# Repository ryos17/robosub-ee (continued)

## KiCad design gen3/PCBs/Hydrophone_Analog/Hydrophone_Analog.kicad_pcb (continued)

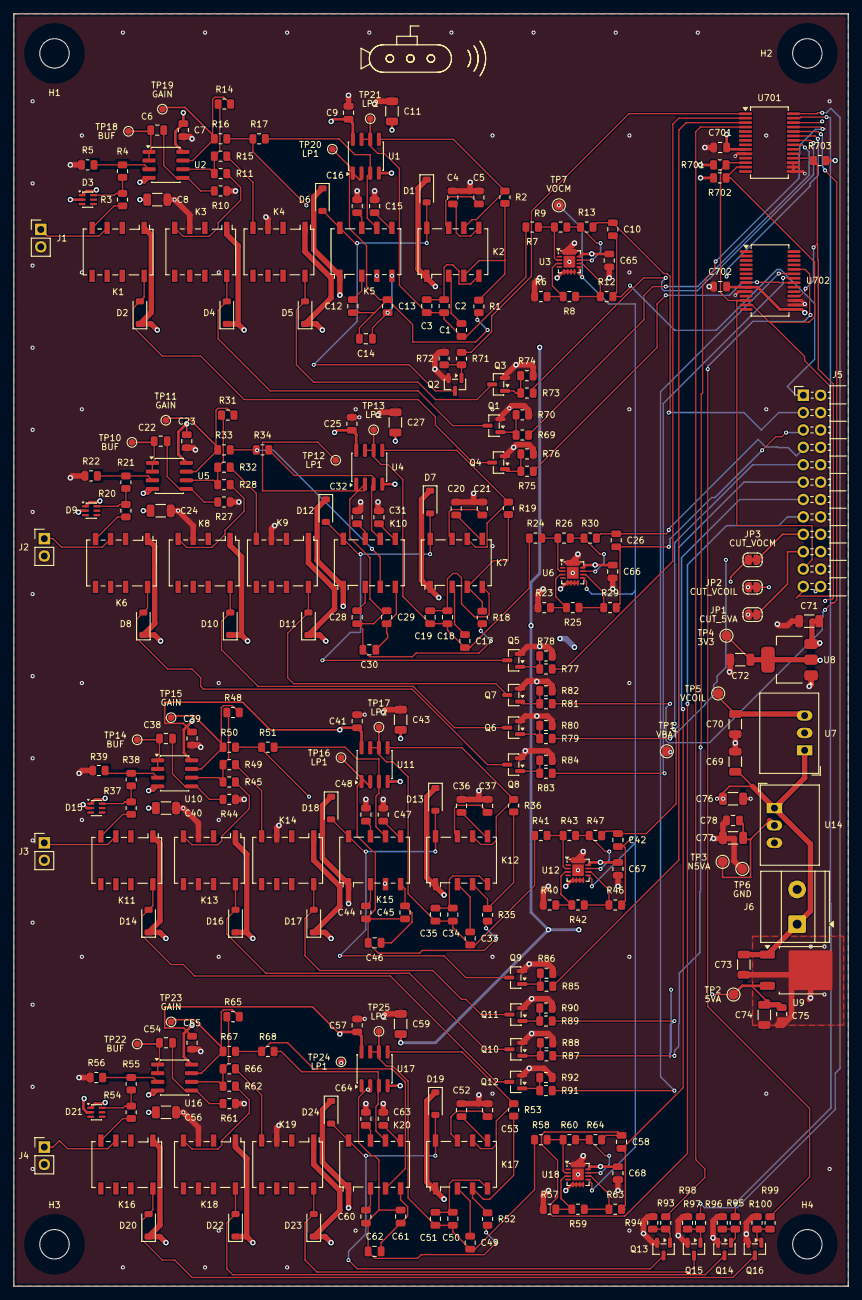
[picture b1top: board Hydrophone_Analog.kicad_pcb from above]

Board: 4 copper layers, 121.9 x 185.9 mm, 297 parts (0 on the bottom side), 181 nets.

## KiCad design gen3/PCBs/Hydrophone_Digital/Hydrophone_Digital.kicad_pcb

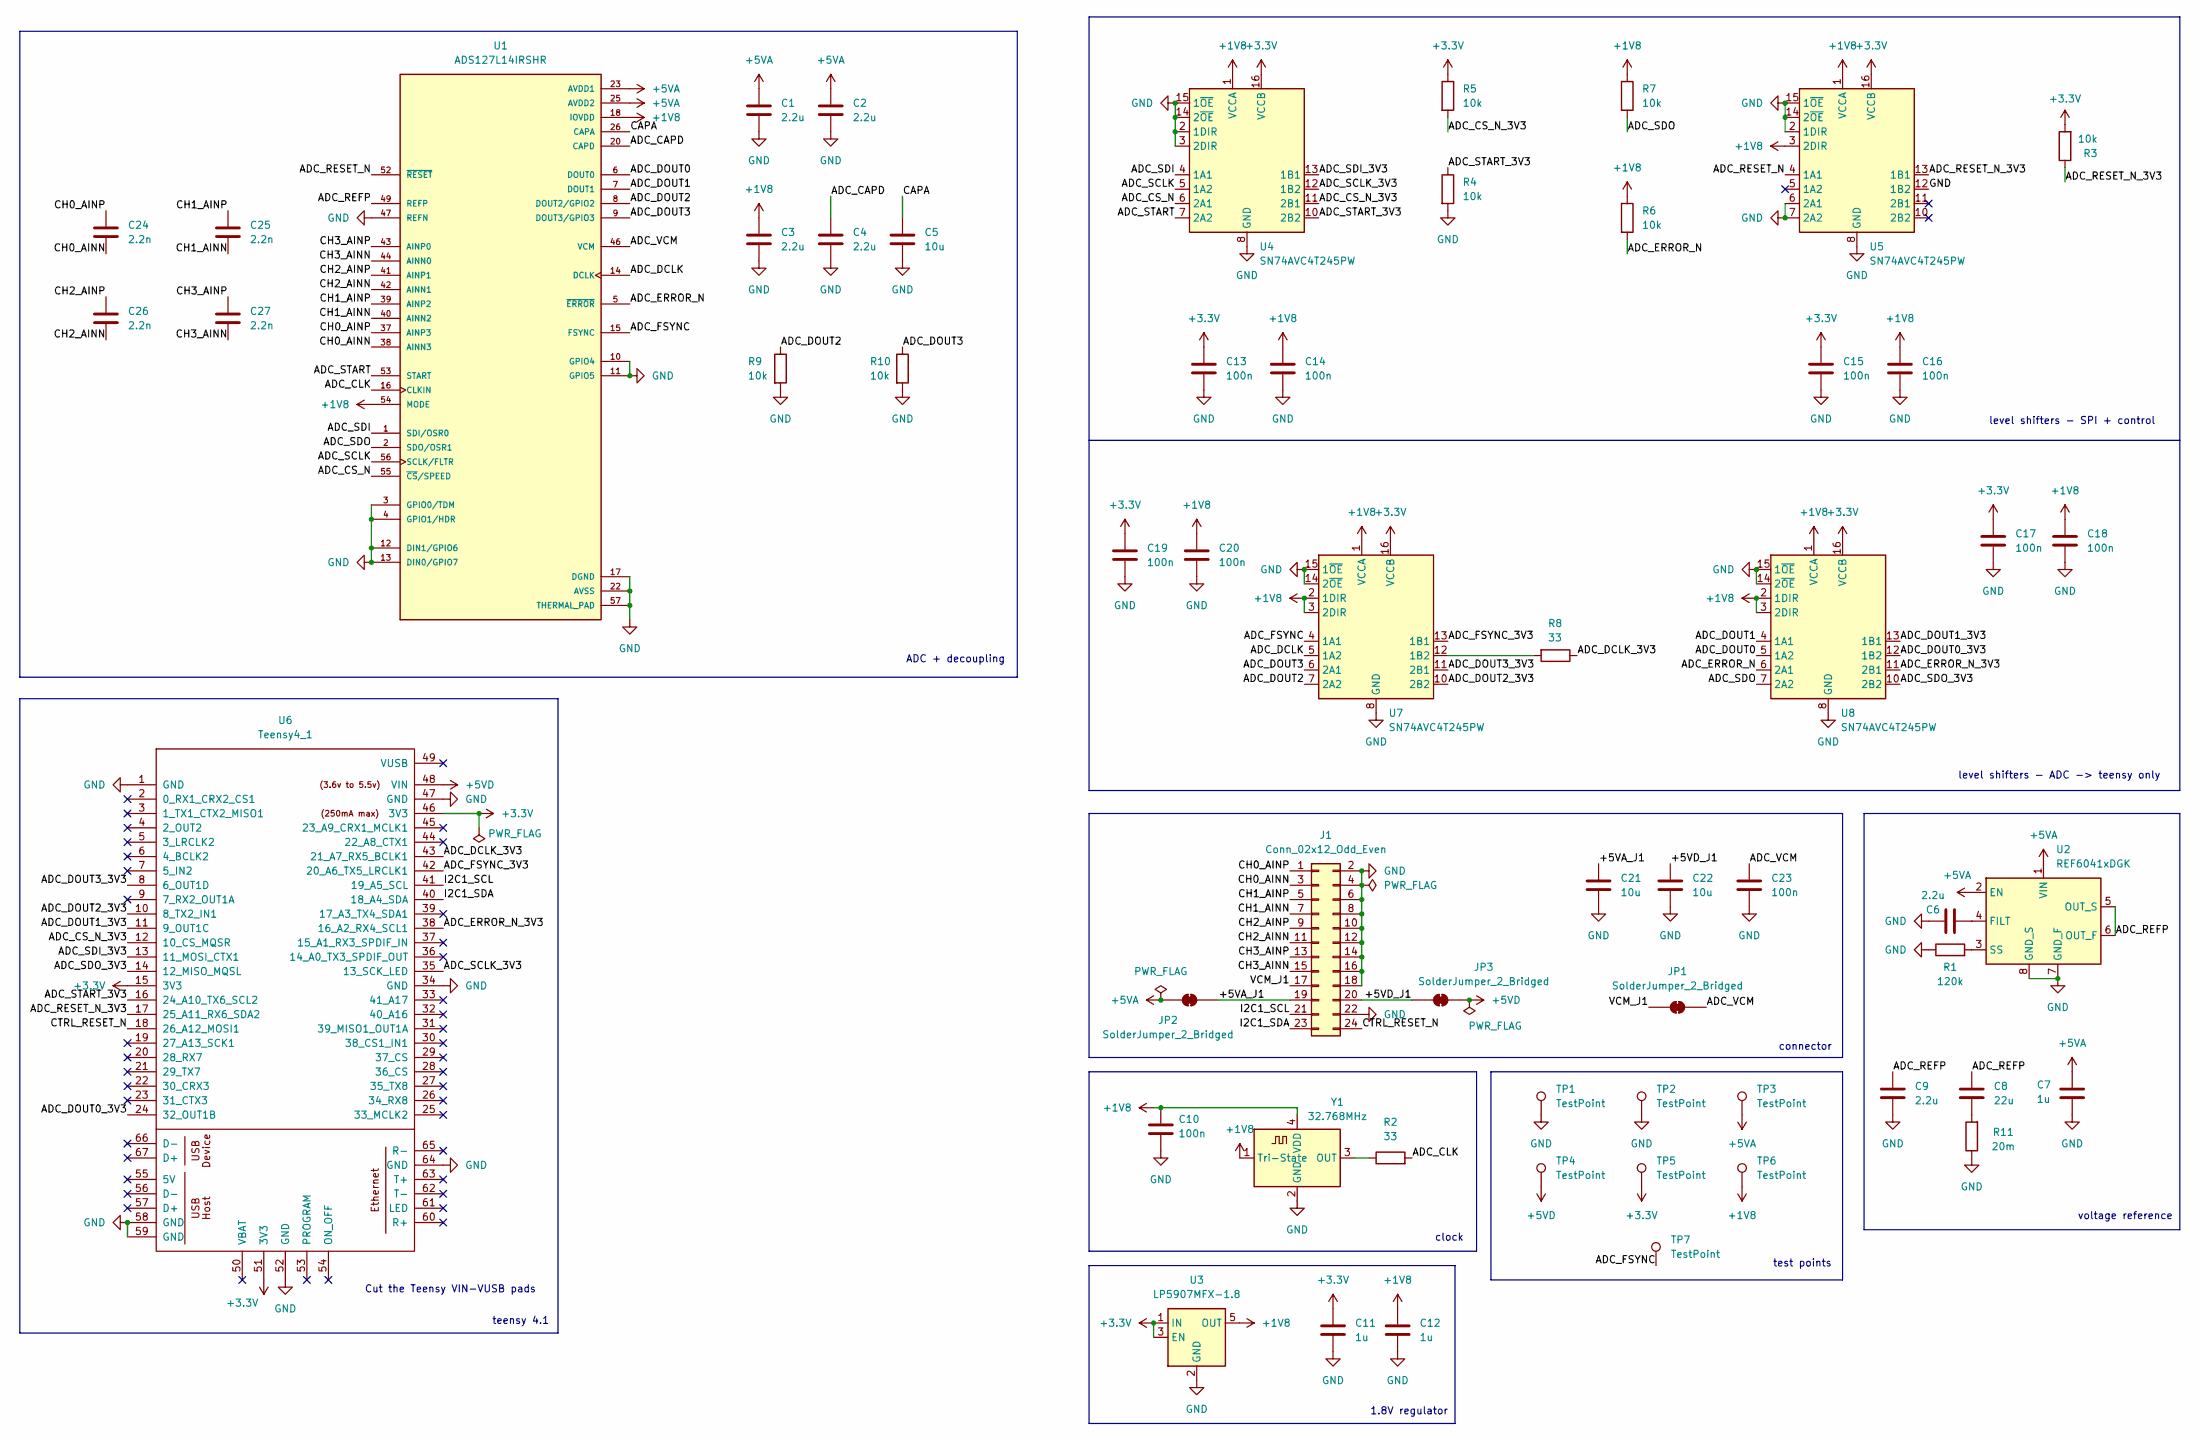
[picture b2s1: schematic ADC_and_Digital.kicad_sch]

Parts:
C1, C2, C3, C4, C6, C9: 2.2u; C_0805_2012Metric_Pad1.18x1.45mm_HandSolder; LCSC C19110
C5, C21, C22: 10u; C_1206_3216Metric_Pad1.33x1.80mm_HandSolder; LCSC C13585
C7, C11, C12: 1u; C_0805_2012Metric_Pad1.18x1.45mm_HandSolder; LCSC C28323
C8: 22u; C_1206_3216Metric_Pad1.33x1.80mm_HandSolder; LCSC C12891
C10, C13, C14, C15, C16, C17, C18, C19, C20, C23: 100n; C_0805_2012Metric_Pad1.18x1.45mm_HandSolder; LCSC C49678
C24, C25, C26, C27: 2.2n; C_0805_2012Metric_Pad1.18x1.45mm_HandSolder; LCSC C28260
J1: Conn_02x12_Odd_Even; PinSocket_2x12_P2.54mm_Horizontal; LCSC C22373936
JP1, JP2, JP3: SolderJumper_2_Bridged; SolderJumper-2_P1.3mm_Bridged_RoundedPad1.0x1.5mm
R1: 120k; R_0805_2012Metric_Pad1.20x1.40mm_HandSolder; LCSC C17436
R2, R8: 33; R_0805_2012Metric_Pad1.20x1.40mm_HandSolder; LCSC C17634
R3, R4, R5, R6, R7, R9, R10: 10k; R_0805_2012Metric_Pad1.20x1.40mm_HandSolder; LCSC C17414
R11: 20m; R_0805_2012Metric_Pad1.20x1.40mm_HandSolder; LCSC C163095
TP1, TP2, TP3, TP4: TestPoint; TestPoint_THTPad_D2.0mm_Drill1.0mm
TP5, TP6: TestPoint; TestPoint_Pad_D1.5mm
TP7: TestPoint; TestPoint_Pad_D1.0mm
U1: ADS127L14IRSHR; IC_ADS127L14IRSHR; PARTREV B; LCSC C46377303
U2: REF6041xDGK; VSSOP-8_3x3mm_P0.65mm; LCSC C2157051
U3: LP5907MFX-1.8; SOT-23-5; LCSC C92498
U4, U5, U7, U8: SN74AVC4T245PW; TSSOP-16_4.4x5mm_P0.65mm; LCSC C81461
U6: Teensy4_1
Y1: 32.768MHz; Oscillator_SMD_ECS_2520MV-xxx-xx-4Pin_2.5x2.0mm; LCSC C5452669

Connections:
+1V8: C3.2, C10.1, C12.1, C14.1, C16.1, C18.1, C20.1, R6.1, R7.1, TP6.1 (1_1), U1.18 (IOVDD), U1.19 (IOVDD), U1.54 (MODE), U3.5 (OUT), U4.1 (VCCA), U5.1 (VCCA), U5.3 (2DIR), U7.1 (VCCA), U7.2 (1DIR), U7.3 (2DIR), U8.1 (VCCA), U8.2 (1DIR), U8.3 (2DIR), Y1.1 (Tri-State), Y1.4 (VDD)
+3.3V: C11.1, C13.1, C15.1, C17.1, C19.1, R3.2, R5.1, TP5.1 (1_1), U3.1 (IN), U3.3 (EN), U4.16 (VCCB), U5.16 (VCCB), U6.15 (3V3), U6.46 (3V3), U6.51 (3V3), U7.16 (VCCB), U8.16 (VCCB)
+5VA: C1.2, C2.2, C7.1, JP2.1 (A), TP3.1 (1_1), U1.23 (AVDD1), U1.24 (AVDD1), U1.25 (AVDD2), U2.1 (VIN), U2.2 (EN)
+5VD: JP3.2 (B), TP4.1 (1_1), U6.48 (VIN)
/ADC_and_Digital/+5VA_J1: C21.1, J1.19, JP2.2 (B)
/ADC_and_Digital/+5VD_J1: C22.1, J1.20, JP3.1 (A)
/ADC_and_Digital/ADC_CAPD: C4.2, U1.20 (CAPD)
/ADC_and_Digital/ADC_CLK: R2.2, U1.16 (CLKIN)
/ADC_and_Digital/ADC_CS_N: U1.55 (~CS/SPEED), U4.6 (2A1)
/ADC_and_Digital/ADC_CS_N_3V3: R5.2, U4.11 (2B1), U6.12 (10_CS_MQSR)
/ADC_and_Digital/ADC_DCLK: U1.14 (DCLK), U7.5 (1A2)
/ADC_and_Digital/ADC_DCLK_3V3: R8.1, U6.43 (21_A7_RX5_BCLK1)
/ADC_and_Digital/ADC_DOUT0: U1.6 (DOUT0), U8.5 (1A2)
/ADC_and_Digital/ADC_DOUT0_3V3: U6.24 (32_OUT1B), U8.12 (1B2)
/ADC_and_Digital/ADC_DOUT1: U1.7 (DOUT1), U8.4 (1A1)
/ADC_and_Digital/ADC_DOUT1_3V3: U6.11 (9_OUT1C), U8.13 (1B1)
/ADC_and_Digital/ADC_DOUT2: R9.1, U1.8 (DOUT2/GPIO2), U7.7 (2A2)
/ADC_and_Digital/ADC_DOUT2_3V3: U6.10 (8_TX2_IN1), U7.10 (2B2)
/ADC_and_Digital/ADC_DOUT3: R10.1, U1.9 (DOUT3/GPIO3), U7.6 (2A1)
/ADC_and_Digital/ADC_DOUT3_3V3: U6.8 (6_OUT1D), U7.11 (2B1)
/ADC_and_Digital/ADC_ERROR_N: R6.2, U1.5 (~ERROR), U8.6 (2A1)
/ADC_and_Digital/ADC_ERROR_N_3V3: U6.38 (16_A2_RX4_SCL1), U8.11 (2B1)
/ADC_and_Digital/ADC_FSYNC: TP7.1 (1_1), U1.15 (FSYNC), U7.4 (1A1)
/ADC_and_Digital/ADC_FSYNC_3V3: U6.42 (20_A6_TX5_LRCLK1), U7.13 (1B1)
/ADC_and_Digital/ADC_REFP: C8.1, C9.1, U1.49 (REFP), U1.50 (REFP), U2.5 (OUT_S), U2.6 (OUT_F)
/ADC_and_Digital/ADC_RESET_N: U1.52 (~RESET), U5.4 (1A1)
/ADC_and_Digital/ADC_RESET_N_3V3: R3.1, U5.13 (1B1), U6.17 (25_A11_RX6_SDA2)
/ADC_and_Digital/ADC_SCLK: U1.56 (SCLK/FLTR), U4.5 (1A2)
/ADC_and_Digital/ADC_SCLK_3V3: U4.12 (1B2), U6.35 (13_SCK_LED)
/ADC_and_Digital/ADC_SDI: U1.1 (SDI/OSR0), U4.4 (1A1)
/ADC_and_Digital/ADC_SDI_3V3: U4.13 (1B1), U6.13 (11_MOSI_CTX1)
/ADC_and_Digital/ADC_SDO: R7.2, U1.2 (SDO/OSR1), U8.7 (2A2)
/ADC_and_Digital/ADC_SDO_3V3: U6.14 (12_MISO_MQSL), U8.10 (2B2)
/ADC_and_Digital/ADC_START: U1.53 (START), U4.7 (2A2)
/ADC_and_Digital/ADC_START_3V3: R4.1, U4.10 (2B2), U6.16 (24_A10_TX6_SCL2)
/ADC_and_Digital/ADC_VCM: C23.1, JP1.2 (B), U1.46 (VCM)
/ADC_and_Digital/CH0_AINN: C24.1, J1.3, U1.38 (AINN3)
/ADC_and_Digital/CH0_AINP: C24.2, J1.1, U1.37 (AINP3)
/ADC_and_Digital/CH1_AINN: C25.1, J1.7, U1.40 (AINN2)
/ADC_and_Digital/CH1_AINP: C25.2, J1.5, U1.39 (AINP2)
/ADC_and_Digital/CH2_AINN: C26.1, J1.11, U1.42 (AINN1)
/ADC_and_Digital/CH2_AINP: C26.2, J1.9, U1.41 (AINP1)
/ADC_and_Digital/CH3_AINN: C27.1, J1.15, U1.44 (AINN0)
/ADC_and_Digital/CH3_AINP: C27.2, J1.13, U1.43 (AINP0)
/ADC_and_Digital/CTRL_RESET_N: J1.24, U6.18 (26_A12_MOSI1)
/ADC_and_Digital/I2C1_SCL: J1.21, U6.41 (19_A5_SCL)
/ADC_and_Digital/I2C1_SDA: J1.23, U6.40 (18_A4_SDA)
/ADC_and_Digital/VCM_J1: J1.17, JP1.1 (A)
CAPA: C5.2, U1.26 (CAPA), U1.27 (CAPA)
GND: C1.1, C2.1, C3.1, C4.1, C5.1, C6.1, C7.2, C9.2, C10.2, C11.2, C12.2, C13.2, C14.2, C15.2, C16.2, C17.2, C18.2, C19.2, C20.2, C21.2, C22.2, C23.2, J1.2, J1.4, J1.6, J1.8, J1.10, J1.12, J1.14, J1.16, J1.18, J1.22, R1.1, R4.2, R9.2, R10.2, R11.1, TP1.1 (1_1), TP2.1 (1_1), U1.3 (GPIO0/TDM), U1.4 (GPIO1/HDR), U1.10 (GPIO4), U1.11 (GPIO5), U1.12 (DIN1/GPIO6), U1.13 (DIN0/GPIO7), U1.17 (DGND), U1.21 (DGND), U1.22 (AVSS), U1.28 (AVSS), U1.29 (AVSS), U1.30 (AVSS), U1.31 (AVSS), U1.32 (AVSS), U1.33 (AVSS), U1.34 (AVSS), U1.35 (AVSS), U1.36 (AVSS), U1.45 (AVSS), U1.47 (REFN), U1.48 (REFN), U1.51 (AVSS), U1.57 (THERMAL_PAD), U2.7 (GND_F), U2.8 (GND_S), U3.2 (GND), U4.2 (1DIR), U4.3 (2DIR), U4.8 (GND), U4.9 (GND), U4.14 (2~OE), U4.15 (1~OE), U5.2 (1DIR), U5.6 (2A1), U5.7 (2A2), U5.8 (GND), U5.9 (GND), U5.12 (1B2), U5.14 (2~OE), U5.15 (1~OE), U6.1 (GND), U6.34 (GND), U6.47 (GND), U6.52 (GND), U6.58 (GND), U6.59 (GND), U6.64 (GND), U7.8 (GND), U7.9 (GND), U7.14 (2~OE), U7.15 (1~OE), U8.8 (GND), U8.9 (GND), U8.14 (2~OE), U8.15 (1~OE), Y1.2 (GND)
unnamed: C8.2, R11.2
unnamed: C6.2, U2.4 (FILT)
unnamed: R1.2, U2.3 (SS)
unnamed: R8.2, U7.12 (1B2)
unnamed: R2.1, Y1.3 (OUT)

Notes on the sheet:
level shifters - SPI + control
Cut the Teensy VIN-VUSB pads
clock
test points
connector
voltage reference
ADC + decoupling
level shifters - ADC -> teensy only
teensy 4.1
1.8V regulator

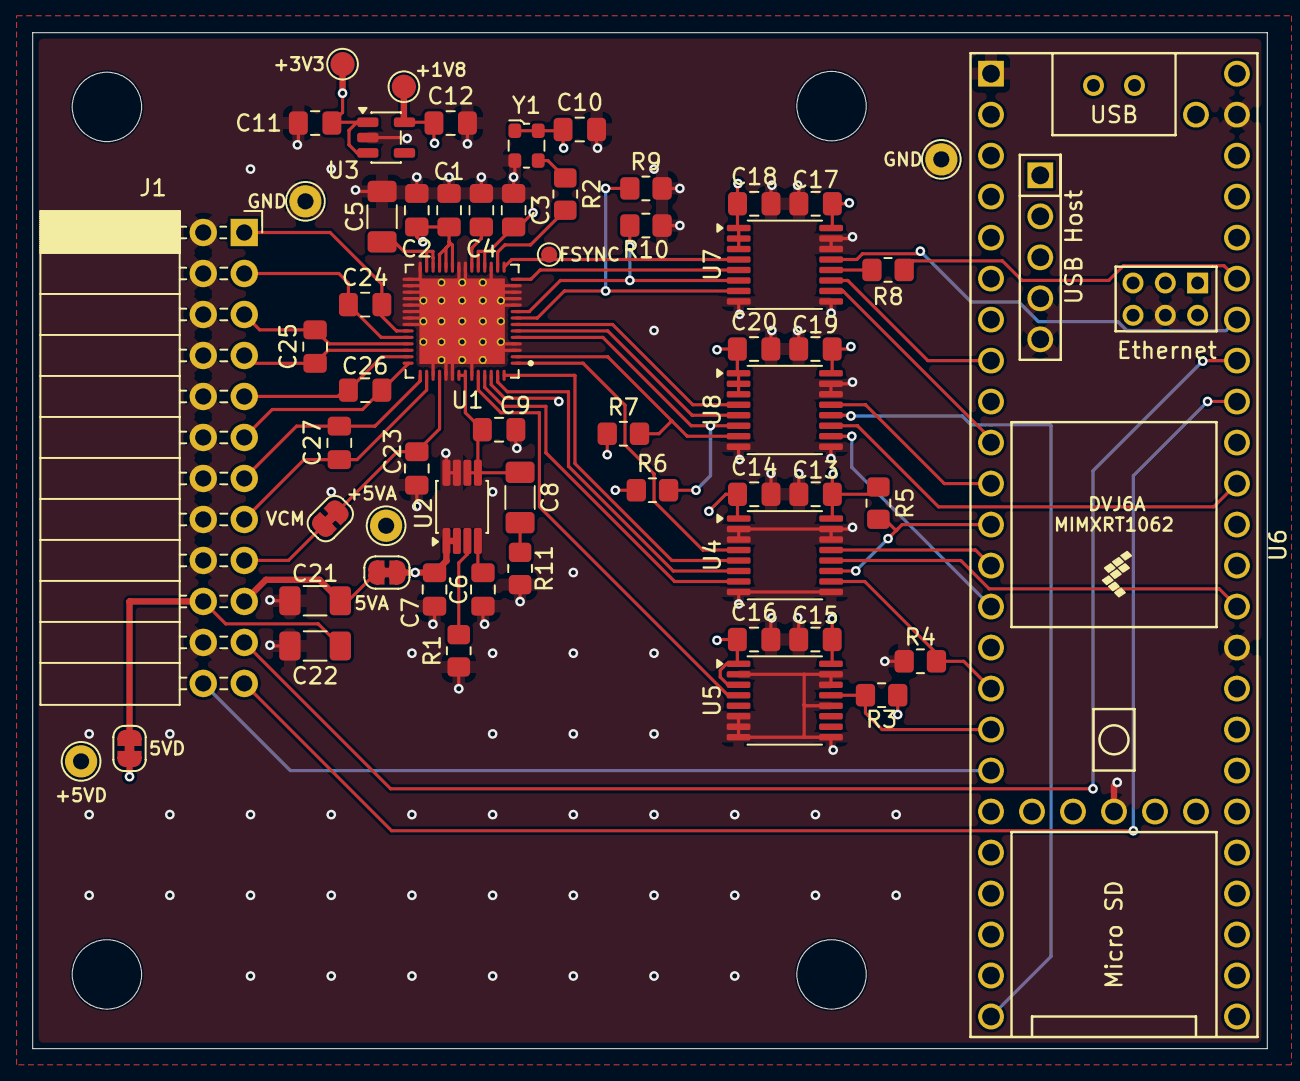
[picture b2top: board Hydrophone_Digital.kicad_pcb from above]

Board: 4 copper layers, 76.5 x 63.0 mm, 62 parts (0 on the bottom side), 55 nets.

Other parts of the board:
H1, H2, H3, H4: MountingHole_4.3mm_M4

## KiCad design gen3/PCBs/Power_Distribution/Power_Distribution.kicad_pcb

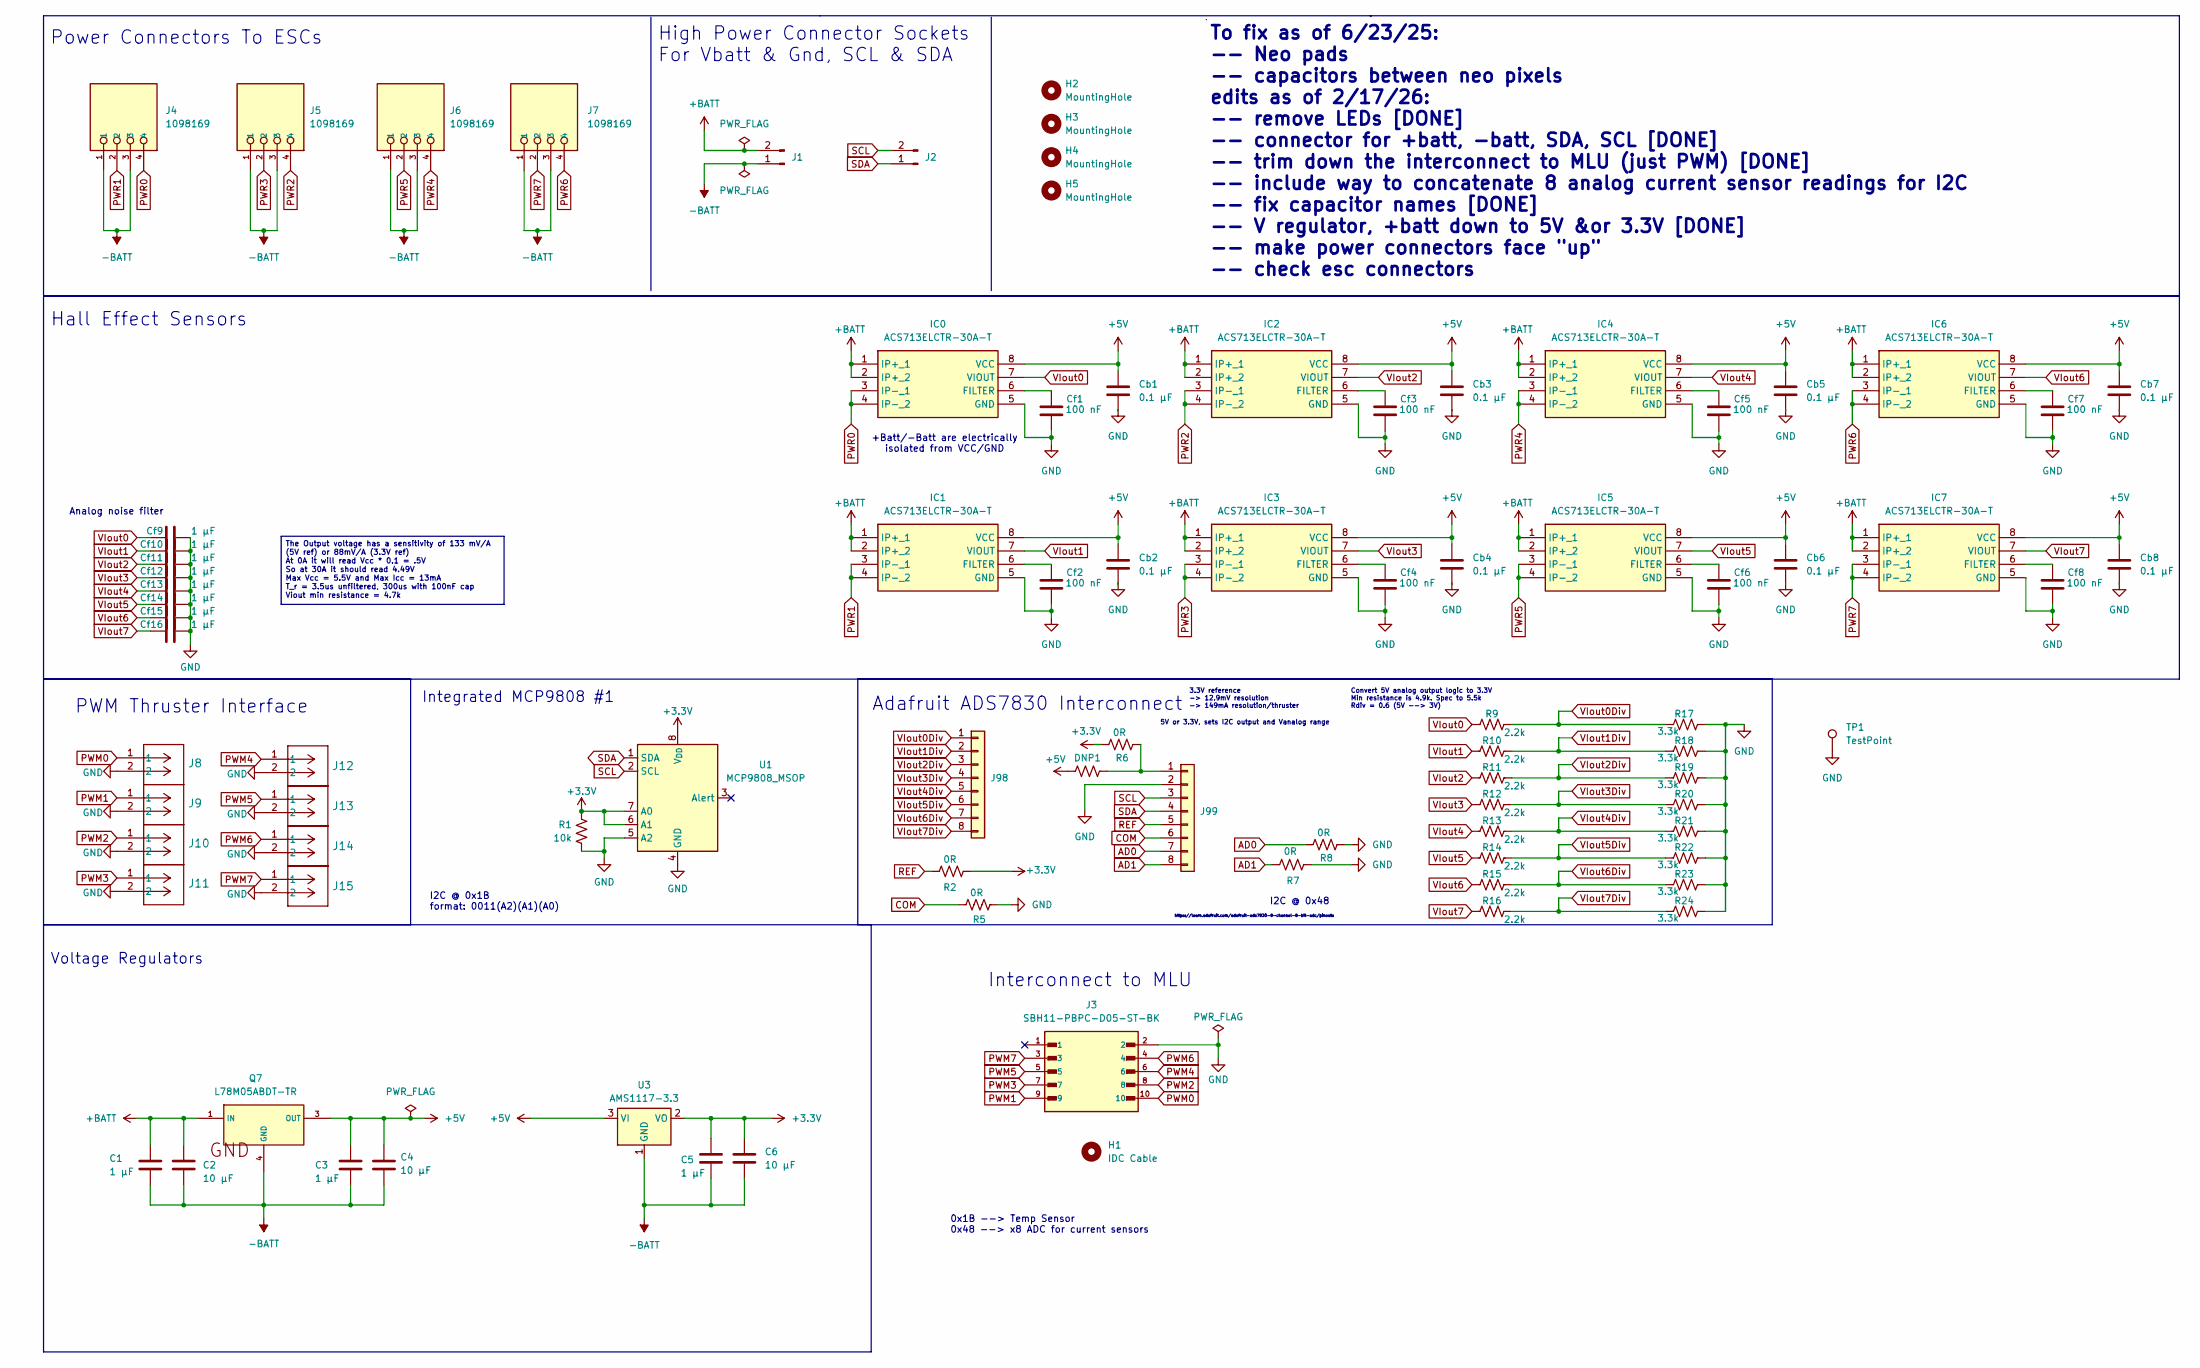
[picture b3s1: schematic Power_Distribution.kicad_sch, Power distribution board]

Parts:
C1, C3, C5: 1 µF; C_0805_2012Metric
C2, C4, C6: 10 µF; C_0805_2012Metric
Cb1, Cb2, Cb3, Cb4, Cb5, Cb6, Cb7, Cb8: 0.1 µF; C_0805_2012Metric_Pad1.18x1.45mm_HandSolder
Cf1, Cf2, Cf3, Cf4, Cf5, Cf6, Cf7, Cf8: 100 nF; C_0805_2012Metric_Pad1.18x1.45mm_HandSolder
Cf9, Cf10, Cf11, Cf12, Cf13, Cf14, Cf15, Cf16: 1 µF; C_0805_2012Metric_Pad1.18x1.45mm_HandSolder
DNP1: 0; R_0805_2012Metric
H1: IDC Cable
H2, H3, H4, H5: MountingHole; MountingHole_4.3mm_M4
IC0, IC1, IC2, IC3, IC4, IC5, IC6, IC7: ACS713ELCTR-30A-T; ACS711ELCTR25ABT; Manufacturer_Part_Number ACS713ELCTR-30A-T
J1: Conn_01x02_Pin; AMASS_XT60IPW-M_1x03_P7.20mm_Horizontal
J2: Conn_01x02_Pin; AMASS_XT30PW-F_1x02_P2.50mm_Horizontal
J3: SBH11-PBPC-D05-ST-BK; SULLINS_SBH11-PBPC-D05-ST-BK; PARTREV J
J4, J5, J6, J7: 1098169; PHOENIX_1098169
J8, J9, J10, J11, J12, J13, J14, J15: 430450212; Molex_Micro-Fit_3.0_43045-0212_2x01_P3.00mm_Vertical
J98, J99: Conn_01x08; PinHeader_1x08_P2.54mm_Vertical
Q7: L78M05ABDT-TR; TO-252-2_L6.5-W6.1-P4.58-LS10.0-TL; LCSC C58069
R1: 10k; R_0805_2012Metric_Pad1.20x1.40mm_HandSolder
R2, R5, R6, R7, R8: 0R; R_0805_2012Metric_Pad1.20x1.40mm_HandSolder
R9, R10, R11, R12, R13, R14, R15, R16: 2.2k; R_0805_2012Metric
R17, R18, R19, R20, R21, R22, R23, R24: 3.3k; R_0805_2012Metric
TP1: TestPoint; TestPoint_Keystone_5019_Miniature
U1: MCP9808_MSOP; MSOP-8_3x3mm_P0.65mm
U3: AMS1117-3.3; SOT-223-3_TabPin2

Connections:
+3.3V: C5.1, C6.1, R1.1, R2.2, R6.1, U1.6 (A1), U1.7 (A0), U1.8 (V_{DD}), U3.2 (VO)
+5V: C3.1, C4.1, Cb1.1, Cb2.1, Cb3.1, Cb4.1, Cb5.1, Cb6.1, Cb7.1, Cb8.1, DNP1.1, IC0.8 (VCC), IC1.8 (VCC), IC2.8 (VCC), IC3.8 (VCC), IC4.8 (VCC), IC5.8 (VCC), IC6.8 (VCC), IC7.8 (VCC), Q7.3 (OUT), U3.3 (VI)
+BATT: C1.1, C2.1, IC0.1 (IP+_1), IC0.2 (IP+_2), IC1.1 (IP+_1), IC1.2 (IP+_2), IC2.1 (IP+_1), IC2.2 (IP+_2), IC3.1 (IP+_1), IC3.2 (IP+_2), IC4.1 (IP+_1), IC4.2 (IP+_2), IC5.1 (IP+_1), IC5.2 (IP+_2), IC6.1 (IP+_1), IC6.2 (IP+_2), IC7.1 (IP+_1), IC7.2 (IP+_2), J1.2, Q7.1 (IN)
-BATT: C1.2, C2.2, C3.2, C4.2, C5.2, C6.2, J1.1, J4.1, J4.3, J5.1, J5.3, J6.1, J6.3, J7.1, J7.3, Q7.4 (GND), U3.1 (GND)
AD0: J99.7, R8.1
AD1: J99.8, R7.1
COM: J99.6, R5.1
GND: Cb1.2, Cb2.2, Cb3.2, Cb4.2, Cb5.2, Cb6.2, Cb7.2, Cb8.2, Cf1.2, Cf2.2, Cf3.2, Cf4.2, Cf5.2, Cf6.2, Cf7.2, Cf8.2, Cf9.2, Cf10.2, Cf11.2, Cf12.2, Cf13.2, Cf14.2, Cf15.2, Cf16.2, IC0.5 (GND), IC1.5 (GND), IC2.5 (GND), IC3.5 (GND), IC4.5 (GND), IC5.5 (GND), IC6.5 (GND), IC7.5 (GND), J3.2, J8.2, J9.2, J10.2, J11.2, J12.2, J13.2, J14.2, J15.2, J99.2, R1.2, R5.2, R7.2, R8.2, R17.2, R18.2, R19.2, R20.2, R21.2, R22.2, R23.2, R24.2, TP1.1, U1.4 (GND), U1.5 (A2)
unnamed: Cf1.1, IC0.6 (FILTER)
unnamed: Cf2.1, IC1.6 (FILTER)
unnamed: Cf3.1, IC2.6 (FILTER)
unnamed: Cf4.1, IC3.6 (FILTER)
unnamed: Cf5.1, IC4.6 (FILTER)
unnamed: Cf6.1, IC5.6 (FILTER)
unnamed: Cf7.1, IC6.6 (FILTER)
unnamed: Cf8.1, IC7.6 (FILTER)
unnamed: DNP1.2, J99.1, R6.2
PWM0: J3.10, J8.1
PWM1: J3.9, J9.1
PWM2: J3.8, J10.1
PWM3: J3.7, J11.1
PWM4: J3.6, J12.1
PWM5: J3.5, J13.1
PWM6: J3.4, J14.1
PWM7: J3.3, J15.1
PWR0: IC0.3 (IP-_1), IC0.4 (IP-_2), J4.4
PWR1: IC1.3 (IP-_1), IC1.4 (IP-_2), J4.2
PWR2: IC2.3 (IP-_1), IC2.4 (IP-_2), J5.4
PWR3: IC3.3 (IP-_1), IC3.4 (IP-_2), J5.2
PWR4: IC4.3 (IP-_1), IC4.4 (IP-_2), J6.4
PWR5: IC5.3 (IP-_1), IC5.4 (IP-_2), J6.2
PWR6: IC6.3 (IP-_1), IC6.4 (IP-_2), J7.4
PWR7: IC7.3 (IP-_1), IC7.4 (IP-_2), J7.2
REF: J99.5, R2.1
SCL: J2.2, J99.3, U1.2 (SCL)
SDA: J2.1, J99.4, U1.1 (SDA)
VIout0: Cf9.1, IC0.7 (VIOUT), R9.1
VIout0Div: J98.1, R9.2, R17.1
VIout1: Cf10.1, IC1.7 (VIOUT), R10.1
VIout1Div: J98.2, R10.2, R18.1
VIout2: Cf11.1, IC2.7 (VIOUT), R11.1
VIout2Div: J98.3, R11.2, R19.1
VIout3: Cf12.1, IC3.7 (VIOUT), R12.1
VIout3Div: J98.4, R12.2, R20.1
VIout4: Cf13.1, IC4.7 (VIOUT), R13.1
VIout4Div: J98.5, R13.2, R21.1
VIout5: Cf14.1, IC5.7 (VIOUT), R14.1
VIout5Div: J98.6, R14.2, R22.1
VIout6: Cf15.1, IC6.7 (VIOUT), R15.1
VIout6Div: J98.7, R15.2, R23.1
VIout7: Cf16.1, IC7.7 (VIOUT), R16.1
VIout7Div: J98.8, R16.2, R24.1

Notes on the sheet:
Interconnect to MLU
Convert 5V analog output logic to 3.3V Min resistance is 4.9k. Spec to 5.5k Rdiv = 0.6 (5V --> 3V)
Analog noise filter
+Batt/-Batt are electrically isolated from VCC/GND
https://learn.adafruit.com/adafruit-ads7830-8-channel-8-bit-adc/pinouts
To fix as of 6/23/25: -- Neo pads -- capacitors between neo pixels edits as of 2/17/26: -- remove LEDs [DONE] -- connector for +batt, -batt, SDA, SCL [DONE] -- trim down the interconnect to MLU (just PWM) [DONE] -- include way to concatenate 8 analog current sensor readings for I2C -- fix capacitor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
I2C @ 0x48
Adafruit ADS7830 Interconnect
5V or 3.3V, sets I2C output and Vanalog range
0x1B --> Temp Sensor 0x48 --> x8 ADC for current sensors
High Power Connector Sockets For Vbatt & Gnd, SCL & SDA
Voltage Regulators
Integrated MCP9808 #1
Power Connectors To ESCs
3.3V reference -> 12.9mV resolution -> 149mA resolution/thruster
PWM Thruster Interface
I2C @ 0x1B format: 0011(A2)(A1)(A0)
Hall Effect Sensors
The Output voltage has a sensitivity of 133 mV/A (5V ref) or 88mV/A (3.3V ref) At 0A it will read Vcc * 0.1 = .5V So at 30A it should read 4.49V Max Vcc = 5.5V and Max Icc = 13mA T_r = 3.5us unfiltered, 300us with 100nF cap Viout min resistance = 4.7k

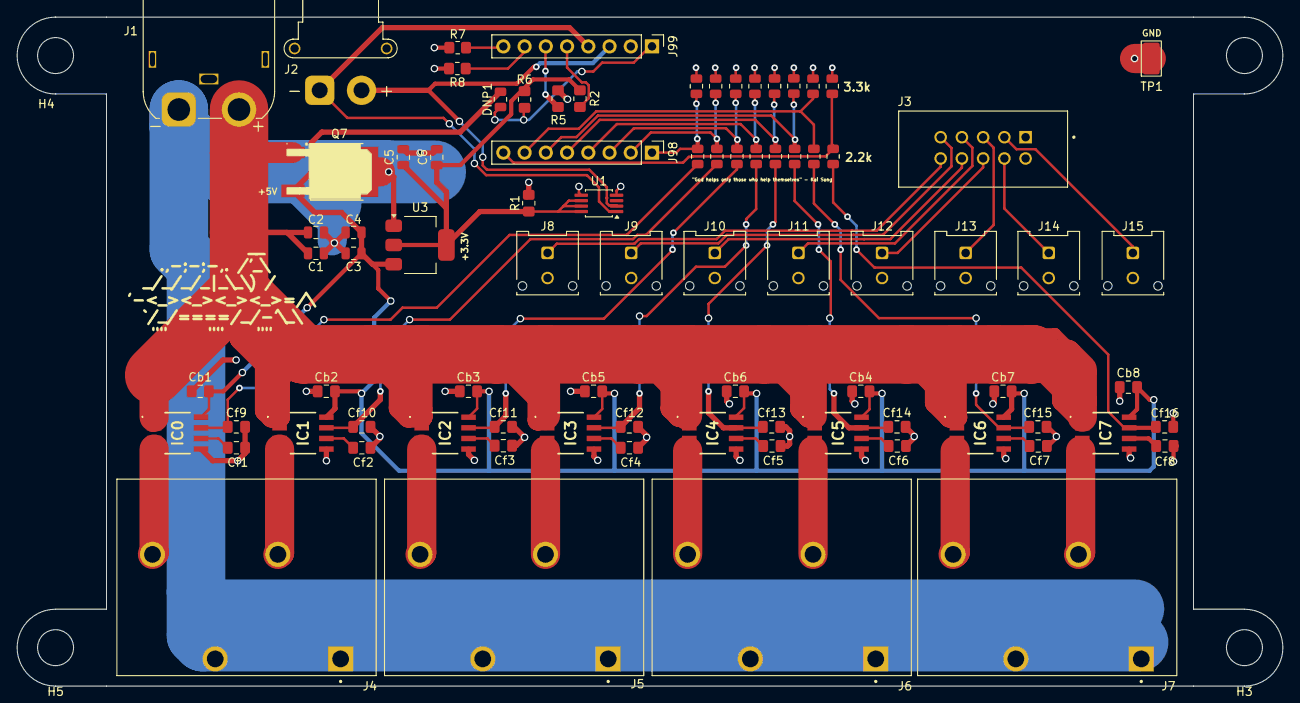
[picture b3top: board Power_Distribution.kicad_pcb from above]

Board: 2 copper layers, 151.4 x 80.0 mm, 86 parts (0 on the bottom side), 52 nets.

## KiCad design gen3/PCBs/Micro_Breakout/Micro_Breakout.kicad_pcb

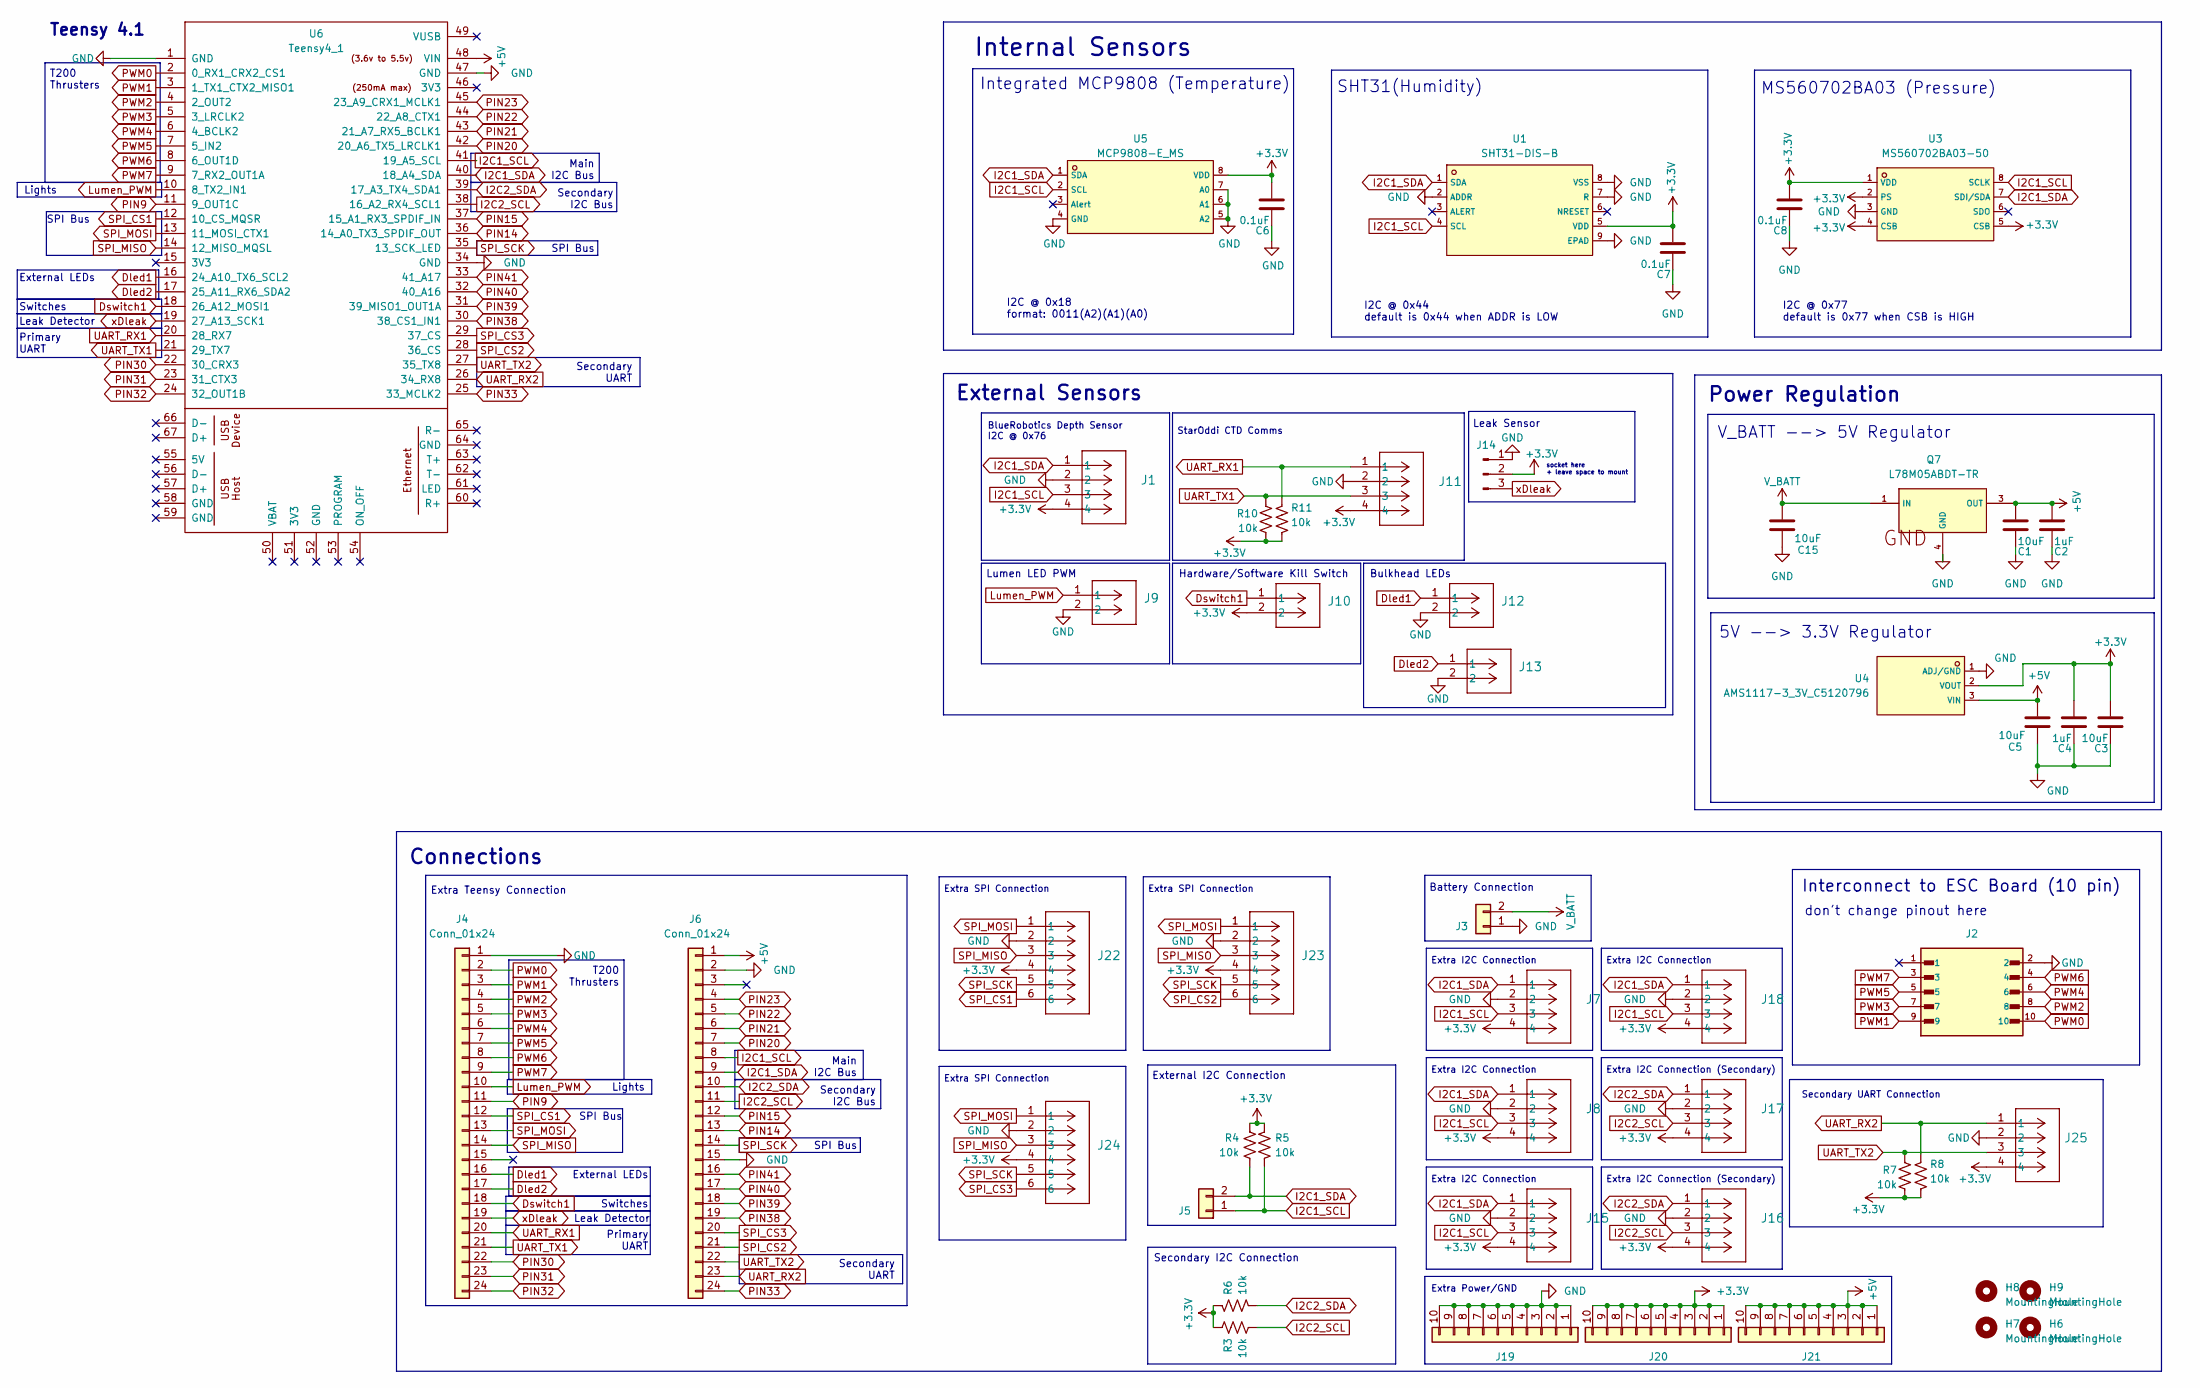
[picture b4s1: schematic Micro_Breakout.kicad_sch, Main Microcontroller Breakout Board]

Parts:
C1, C3, C5, C15: 10uF; C_0805_2012Metric_Pad1.18x1.45mm_HandSolder
C2, C4: 1uF; C_0805_2012Metric_Pad1.18x1.45mm_HandSolder
C6, C7, C8: 0.1uF; C_0805_2012Metric_Pad1.18x1.45mm_HandSolder
H6, H7, H8, H9: MountingHole; MountingHole_4.3mm_M4
J1: BlueRobotics Depth Sensor; 430450412
J2: Interconnect; SBH11-PBPC-D05-ST-BK; PARTREV J
J3: External Battery; AMASS_XT60PW-F_1x02_P7.20mm_Horizontal
J4, J6: Conn_01x24; PinHeader_1x24_P2.54mm_Vertical
J5: External I2C; AMASS_XT30PW-F_1x02_P2.50mm_Horizontal
J7: Extra I2C #1; 430450412
J8: Extra I2C #2; 430450412
J9: Lumen PWM; 430450212
J10: Kill Switch; 430450212
J11: StarOddi CTD Comms; 430450412
J12: LED1; 430450212
J13: LED2; 430450212
J14: Leak Sensor; PinHeader_1x03_P2.54mm_Vertical
J15: Extra I2C #3; 430450412
J16: Extra I2C #6; 430450412
J17: Extra I2C #5; 430450412
J18: Extra I2C #4; 430450412
J19: GND Line; PinHeader_1x10_P2.54mm_Vertical
J20: 3.3V Line; PinHeader_1x10_P2.54mm_Vertical
J21: 5V Line; PinHeader_1x10_P2.54mm_Vertical
J22: Extra SPI #1; 430450612
J23: Extra SPI #2; 430450612
J24: Extra SPI #3; 430450612
J25: Secondary UART; 430450412
Q7: L78M05ABDT-TR; LCSC C58069
R3, R4, R5, R6, R7, R8, R10, R11: 10k; R_0805_2012Metric_Pad1.20x1.40mm_HandSolder
U1: SHT31-DIS-B; LCSC C80862
U3: MS560702BA03-50; LCSC C97627
U4: AMS1117-3_3V_C5120796; LCSC C5120796
U5: MCP9808-E_MS; LCSC C94847
U6: Teensy4_1

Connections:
+3.3V: C3.1, C4.1, C6.1, C7.1, C8.1, J1.4, J7.4, J8.4, J10.2, J11.4, J14.2, J15.4, J16.4, J17.4, J18.4, J20.1, J20.2, J20.3, J20.4, J20.5, J20.6, J20.7, J20.8, J20.9, J20.10, J22.4, J23.4, J24.4, J25.4, R3.1, R4.1, R5.1, R6.1, R7.2, R8.2, R10.2, R11.2, U1.5 (VDD), U3.1 (VDD), U3.2 (PS), U3.4 (CSB), U3.5 (CSB), U4.2 (VOUT), U5.8 (VDD)
+5V: C1.1, C2.1, C5.1, J6.1, J21.1, J21.2, J21.3, J21.4, J21.5, J21.6, J21.7, J21.8, J21.9, J21.10, Q7.3 (OUT), U4.3 (VIN), U6.48 (VIN)
Dled1: J4.16, J12.1, U6.16 (24_A10_TX6_SCL2)
Dled2: J4.17, J13.1, U6.17 (25_A11_RX6_SDA2)
Dswitch1: J4.18, J10.1, U6.18 (26_A12_MOSI1)
GND: C1.2, C2.2, C3.2, C4.2, C5.2, C6.2, C7.2, C8.2, C15.2, J1.2, J2.2, J3.1, J4.1, J6.2, J6.15, J7.2, J8.2, J9.2, J11.2, J12.2, J13.2, J14.1, J15.2, J16.2, J17.2, J18.2, J19.1, J19.2, J19.3, J19.4, J19.5, J19.6, J19.7, J19.8, J19.9, J19.10, J22.2, J23.2, J24.2, J25.2, Q7.4 (GND), U1.2 (ADDR), U1.7 (R), U1.8 (VSS), U1.9 (EPAD), U3.3 (GND), U4.1 (ADJ/GND), U5.4 (GND), U5.5 (A2), U5.6 (A1), U5.7 (A0), U6.1 (GND), U6.34 (GND), U6.47 (GND)
I2C1_SCL: J1.3, J5.1, J6.8, J7.3, J8.3, J15.3, J18.3, R5.2, U1.4 (SCL), U3.8 (SCLK), U5.2 (SCL), U6.41 (19_A5_SCL)
I2C1_SDA: J1.1, J5.2, J6.9, J7.1, J8.1, J15.1, J18.1, R4.2, U1.1 (SDA), U3.7 (SDI/SDA), U5.1 (SDA), U6.40 (18_A4_SDA)
I2C2_SCL: J6.11, J16.3, J17.3, R3.2, U6.38 (16_A2_RX4_SCL1)
I2C2_SDA: J6.10, J16.1, J17.1, R6.2, U6.39 (17_A3_TX4_SDA1)
Lumen_PWM: J4.10, J9.1, U6.10 (8_TX2_IN1)
PIN9: J4.11, U6.11 (9_OUT1C)
PIN14: J6.13, U6.36 (14_A0_TX3_SPDIF_OUT)
PIN15: J6.12, U6.37 (15_A1_RX3_SPDIF_IN)
PIN20: J6.7, U6.42 (20_A6_TX5_LRCLK1)
PIN21: J6.6, U6.43 (21_A7_RX5_BCLK1)
PIN22: J6.5, U6.44 (22_A8_CTX1)
PIN23: J6.4, U6.45 (23_A9_CRX1_MCLK1)
PIN30: J4.22, U6.22 (30_CRX3)
PIN31: J4.23, U6.23 (31_CTX3)
PIN32: J4.24, U6.24 (32_OUT1B)
PIN33: J6.24, U6.25 (33_MCLK2)
PIN38: J6.19, U6.30 (38_CS1_IN1)
PIN39: J6.18, U6.31 (39_MISO1_OUT1A)
PIN40: J6.17, U6.32 (40_A16)
PIN41: J6.16, U6.33 (41_A17)
PWM0: J2.10, J4.2, U6.2 (0_RX1_CRX2_CS1)
PWM1: J2.9, J4.3, U6.3 (1_TX1_CTX2_MISO1)
PWM2: J2.8, J4.4, U6.4 (2_OUT2)
PWM3: J2.7, J4.5, U6.5 (3_LRCLK2)
PWM4: J2.6, J4.6, U6.6 (4_BCLK2)
PWM5: J2.5, J4.7, U6.7 (5_IN2)
PWM6: J2.4, J4.8, U6.8 (6_OUT1D)
PWM7: J2.3, J4.9, U6.9 (7_RX2_OUT1A)
SPI_CS1: J4.12, J22.6, U6.12 (10_CS_MQSR)
SPI_CS2: J6.21, J23.6, U6.28 (36_CS)
SPI_CS3: J6.20, J24.6, U6.29 (37_CS)
SPI_MISO: J4.14, J22.3, J23.3, J24.3, U6.14 (12_MISO_MQSL)
SPI_MOSI: J4.13, J22.1, J23.1, J24.1, U6.13 (11_MOSI_CTX1)
SPI_SCK: J6.14, J22.5, J23.5, J24.5, U6.35 (13_SCK_LED)
UART_RX1: J4.20, J11.1, R11.1, U6.20 (28_RX7)
UART_RX2: J6.23, J25.1, R8.1, U6.26 (34_RX8)
UART_TX1: J4.21, J11.3, R10.1, U6.21 (29_TX7)
UART_TX2: J6.22, J25.3, R7.1, U6.27 (35_TX8)
V_BATT: C15.1, J3.2, Q7.1 (IN)
xDleak: J4.19, J14.3, U6.19 (27_A13_SCK1)

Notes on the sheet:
Secondary I2C Bus
Hardware/Software Kill Switch
don't change pinout here
Primary UART
External I2C Connection
Power Regulation
Extra SPI Connection
Extra I2C Connection
I2C @ 0x44 default is 0x44 when ADDR is LOW
I2C @ 0x77 default is 0x77 when CSB is HIGH
Switches
Battery Connection
Lumen LED PWM
StarOddi CTD Comms
T200 Thrusters
SHT31(Humidity)
Extra I2C Connection (Secondary)
External LEDs
5V --> 3.3V Regulator
Leak Detector
Secondary UART
Internal Sensors
BlueRobotics Depth Sensor I2C @ 0x76
Bulkhead LEDs
Lights
Main I2C Bus
I2C @ 0x18 format: 0011(A2)(A1)(A0)
socket here + leave space to mount
Interconnect to ESC Board (10 pin)
Secondary I2C Connection
Extra Power/GND
Connections
Teensy 4.1
Leak Sensor
SPI Bus
Secondary UART Connection
External Sensors
Extra Teensy Connection
MS560702BA03 (Pressure)
V_BATT --> 5V Regulator

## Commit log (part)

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2025-11-12 added internal temperature to STABLE
2026-02-21 refractored code
2026-02-21 test file
2026-02-21 added gen3 board
2026-02-21 test message
2026-02-21 reformated and refactored micro pcb board
2026-02-21 adding Battery_Boards directory
2026-02-21 Add shared robosub KiCad libraries, importorted 5v regulator, made some changes to battery management board
2026-02-21 power dist fixes 1
2026-02-21 power distttt
2026-02-21 initial designs
2026-02-22 schematics of microboard done
2026-02-22 fixed up the battery board. should be good to order soon
2026-02-22 added caps to micro breakout
2026-02-22 added back 5V regulator footprints
2026-02-22 microcontroller breakout board completed!!
2026-02-22 power dist board
2026-02-22 bms board finished
2026-02-25 power dist final?
2026-02-25 added to_order
2026-02-25 fixed pinout for ribbon
2026-02-25 fixed GND plane
2026-02-27 to_order has the 3 main pcbs consolidated. pcbs have been put into production
2026-04-08 connected missing SDA SCL connection on gen 3 micro board
2026-04-15 added all custom in robosub_3d_models
2026-04-15 no errors for updating symbol
2026-04-15 works
2026-04-15 jlc_to_robosub working, and all parts are updated.
2026-04-15 updated parts to include jlcpcb as library path
2026-04-15 deleted and renamed unnecessary step and footprints
2026-04-15 fixed
2026-04-15 jlc_to_robosub is completely working
2026-04-15 edited spreadsheet
2026-04-15 Updated the whole schematic to now include 3d model
2026-04-21 wired correctly gen3 sub
2026-04-21 editted
2026-04-22 some notes to self in new board
2026-04-29 fixed cap on microbreakout
2026-05-20 power distribution board updates
